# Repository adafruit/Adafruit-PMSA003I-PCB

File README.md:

## Adafruit PMSA003I Air Quality Breakout - STEMMA QT / Qwiic PCB

<a href="http://www.adafruit.com/products/4632"><br/>
Click here to purchase one from the Adafruit shop</a>

PCB files for the Adafruit PMSA003I Air Quality Breakout - STEMMA QT / Qwiic.

Format is EagleCAD schematic and board layout
* https://www.adafruit.com/product/4632

### Description

Breathe easy, knowing that you can track and sense the quality of the air around you with this Adafruit PMSA003I Air Quality Breakout. This sensor is great for monitoring air quality, in a compact plug-in format.

Best of all, unlike almost all other sensors we've seen that are UART interface, this one is I2C interface, which makes it a great match for single board Linux computers like Raspberry Pi, or even plain Arduino UNO's that normally would use software serial.

If you're an I2C fan (who isn't?), we've included two of our handy dandy SparkFun Qwiic compatible STEMMA QT connectors for the I2C bus so you don't even need to solder! Plug and play with other 'QT boards and sensors to add quick air quality sensing.

This sensor uses laser scattering to radiate suspending particles in the air, then collects scattering light to obtain the curve of scattering light change with time. The microprocessor calculates equivalent particle diameter and the number of particles with different diameters per unit volume.

The I2C data stream updates once per second, you'll get:

* PM1.0, PM2.5 and PM10.0 concentration in both standard & environmental units
* Particulate matter per 0.1L air, categorized into 0.3um, 0.5um, 1.0um, 2.5um, 5.0um and 10um size bins

As well as checksum, in binary format.

Each order comes with one fully assembled sensor module breakout, including some header if you'd like to solder it to a breadboard. The breakout board has a 5V mini boost circuit so you can power it from 3.3V and 5V and the motor will run just fine

Lastly, it wouldn't be an Adafruit breakout if it didn't come with libraries for Arduino and CircuitPython or Python that will read and checksum data, and print it out in human-readable format.

If you prefer the bare sensor module by itself, we carry it on this page.

### License

Adafruit invests time and resources providing this open source design, please support Adafruit and open-source hardware by purchasing products from [Adafruit](https://www.adafruit.com)!

Designed by Limor Fried/Ladyada for Adafruit Industries.

Creative Commons Attribution/Share-Alike, all text above must be included in any redistribution.
See license.txt for additional details.

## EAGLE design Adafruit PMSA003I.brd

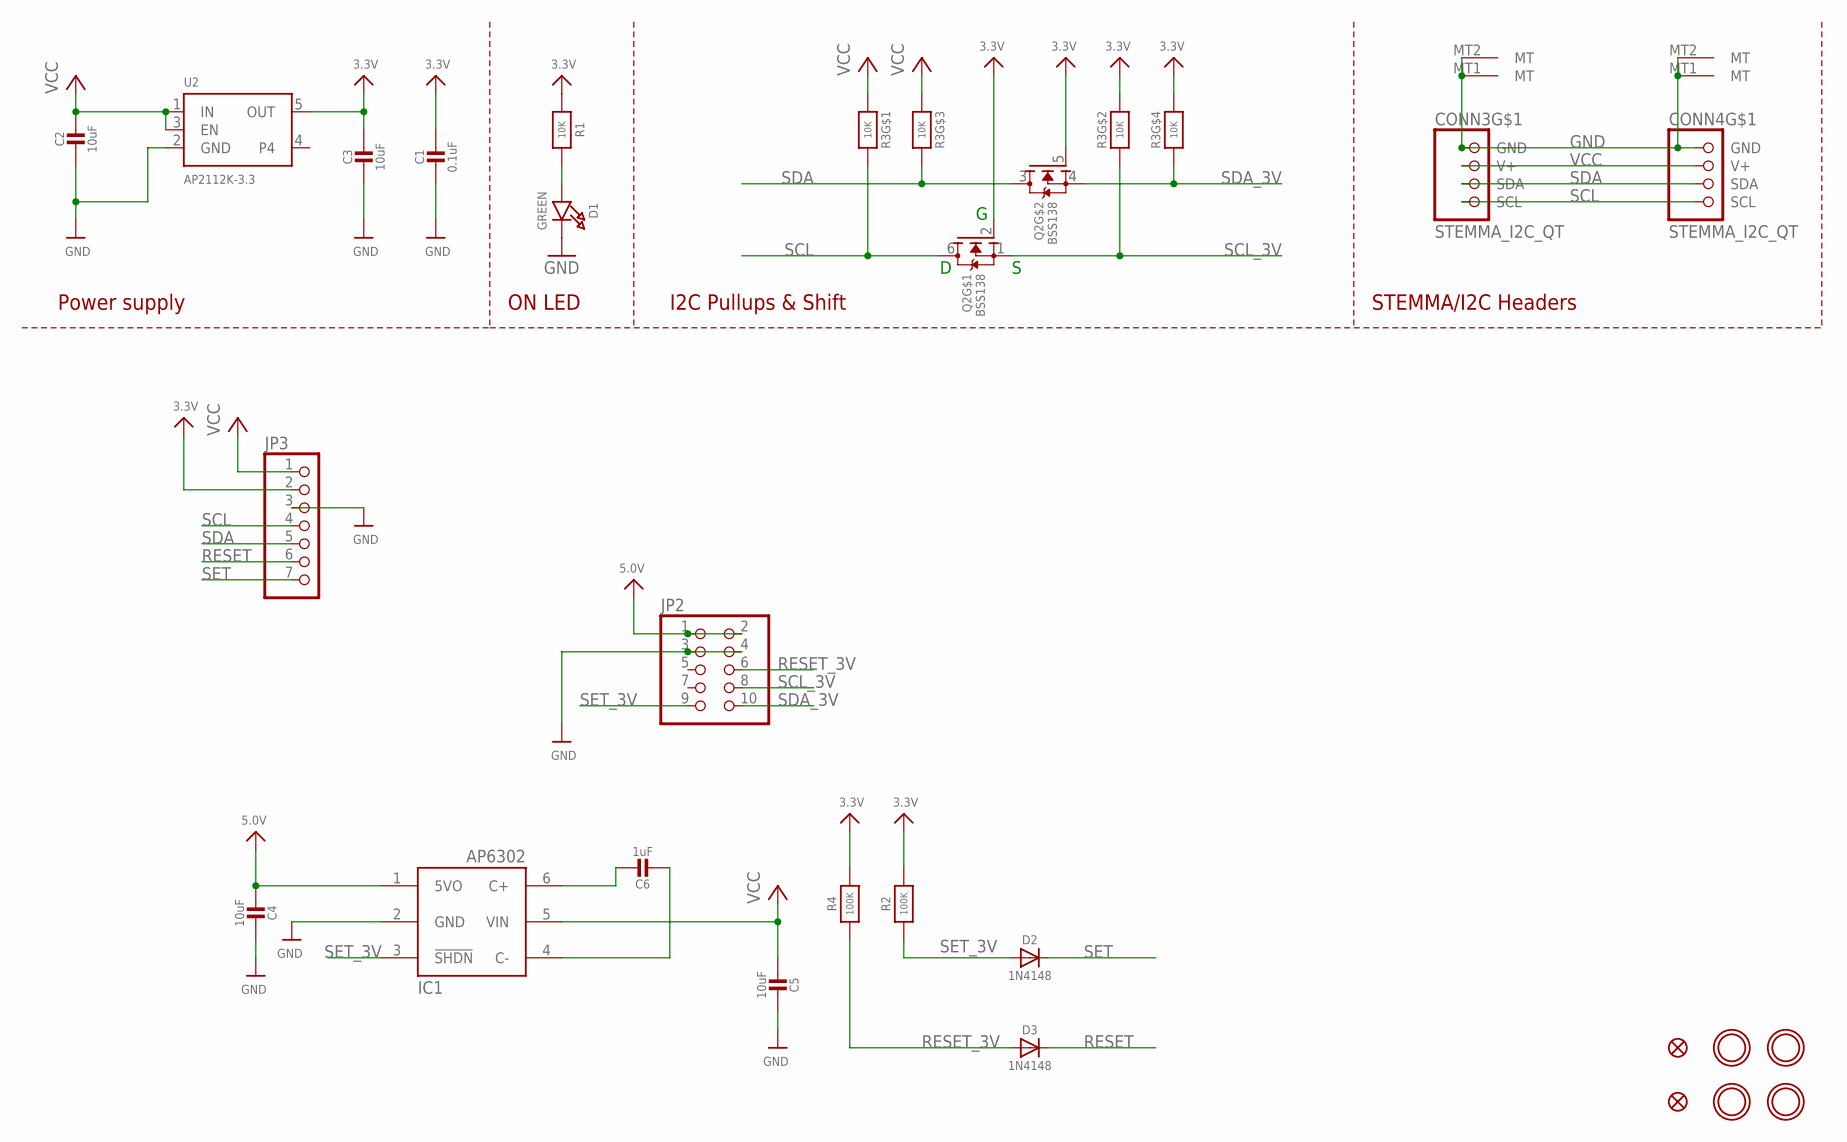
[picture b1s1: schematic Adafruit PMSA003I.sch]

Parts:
C1: 0.1uF; 0603-NO
C2, C3, C4: 10uF; 0805-NO
C5: 10uF; 0805_10MGAP
C6: 1uF; 0805-NO
CONN3, CONN4: STEMMA_I2C_QT; JST_SH4
D1: GREEN; CHIPLED_0603_NOOUTLINE
D2, D3: 1N4148; SOD-323
FID3, FID4: FIDUCIAL_1MM
IC1: AP3602/RT9361; SOT23-6
JP2: HEADER-2X51.27MM; 2X05_1.27MM_SMT
JP3: HEADER-1X770MIL; 1X07_ROUND_70
Q2: BSS138; SOT363
R1: 10K; 0603-NO
R2, R4: 100K; 0603-NO
R3: 10K; RESPACK_4X0603
U2: AP2112K-3.3; SOT23-5
U$1, U$17, U$19, U$21: MOUNTINGHOLE2.5; MOUNTINGHOLE_2.5_PLATED

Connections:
3.3V: C1.1, C3.1, JP3.2, Q2.2 (G), Q2.5 (G), R1.1, R2.1, R3.2 (1), R3.4 (1), R4.1, U2.5 (OUT)
5.0V: C4.1, IC1.1 (5VO), JP2.1, JP2.2
GND: C1.2, C2.2, C3.2, C4.2, C5.2, CONN3.1 (GND), CONN3.MT1 (MT), CONN3.MT2 (MT), CONN4.1 (GND), CONN4.MT1 (MT), CONN4.MT2 (MT), D1.C, IC1.2 (GND), JP2.3, JP2.4, JP3.3, U2.2 (GND)
unnamed: D1.A, R1.2
unnamed: C6.2, IC1.6 (C+)
unnamed: C6.1, IC1.4 (C-)
RESET: D3.C, JP3.6
RESET_3V: D3.A, JP2.6, R4.2
SCL: CONN3.4 (SCL), CONN4.4 (SCL), JP3.4, Q2.6 (D), R3.8 (2)
SCL_3V: JP2.8, Q2.1 (S), R3.7 (2)
SDA: CONN3.3 (SDA), CONN4.3 (SDA), JP3.5, Q2.3 (D), R3.6 (2)
SDA_3V: JP2.10, Q2.4 (S), R3.5 (2)
SET: D2.C, JP3.7
SET_3V: D2.A, IC1.3 (!SHDN), JP2.9, R2.2
VCC: C2.1, C5.1, CONN3.2 (V+), CONN4.2 (V+), IC1.5 (VIN), JP3.1, R3.1, R3.3 (1), U2.1 (IN), U2.3 (EN)

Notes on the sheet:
I2C Pullups & Shift
STEMMA/I2C Headers
ON LED
Power supply

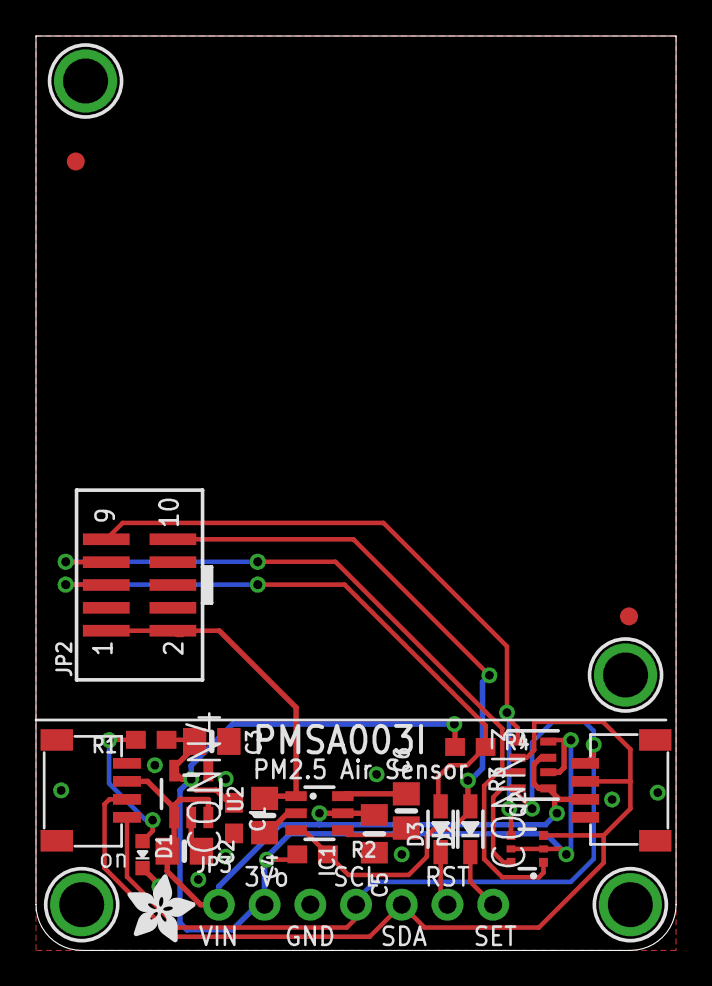
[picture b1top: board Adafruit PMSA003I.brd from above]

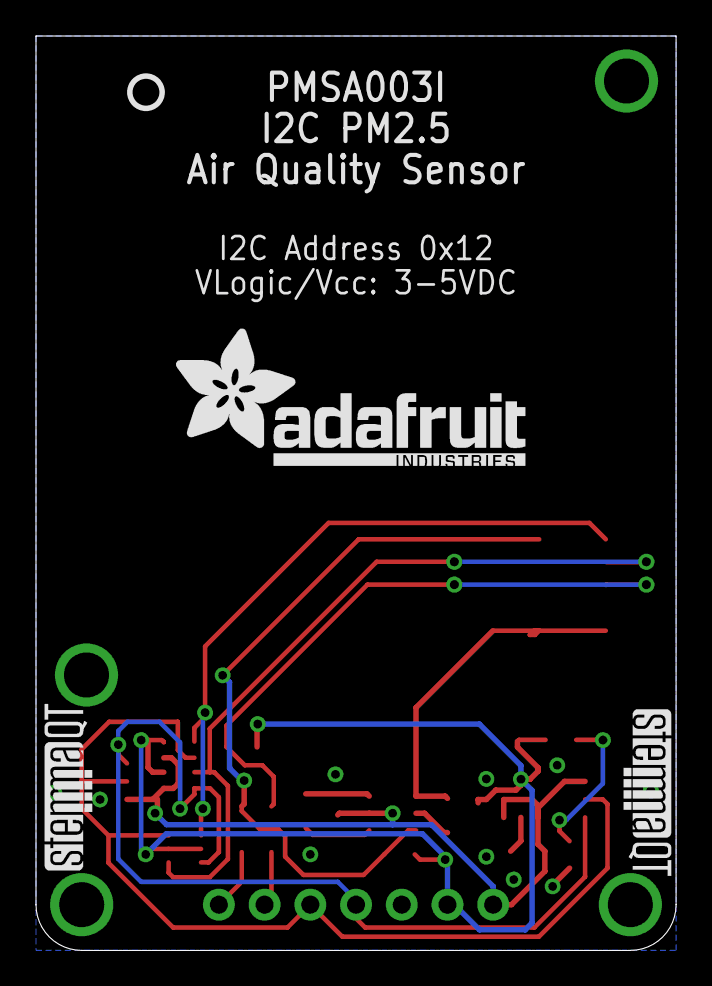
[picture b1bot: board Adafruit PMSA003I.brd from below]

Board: 2 copper layers, 35.6 x 50.8 mm, 31 parts (4 on the bottom side), 15 nets.

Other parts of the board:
U$22: ADAFRUIT_3.5MM
U$25: PCBFEAT-REV-040
U$28: ADAFRUIT_TEXT_20MM
U$30, U$31: STEMMAQT

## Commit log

2020-07-08 Add board files.

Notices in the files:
parts and their libraries:
microbuilder: This work is placed in the public domain, and may be freely used for commercial and non-commercial work with the following conditions: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
